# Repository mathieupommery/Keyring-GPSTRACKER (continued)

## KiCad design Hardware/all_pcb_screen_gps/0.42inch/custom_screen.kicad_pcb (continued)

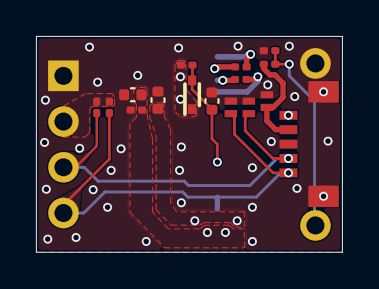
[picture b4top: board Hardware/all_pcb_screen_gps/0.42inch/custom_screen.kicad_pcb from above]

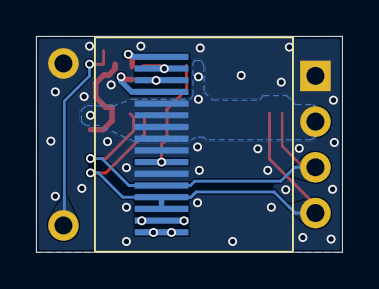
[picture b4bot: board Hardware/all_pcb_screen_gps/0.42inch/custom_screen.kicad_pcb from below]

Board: 2 copper layers, 17.0 x 12.0 mm, 18 parts (2 on the bottom side), 13 nets.

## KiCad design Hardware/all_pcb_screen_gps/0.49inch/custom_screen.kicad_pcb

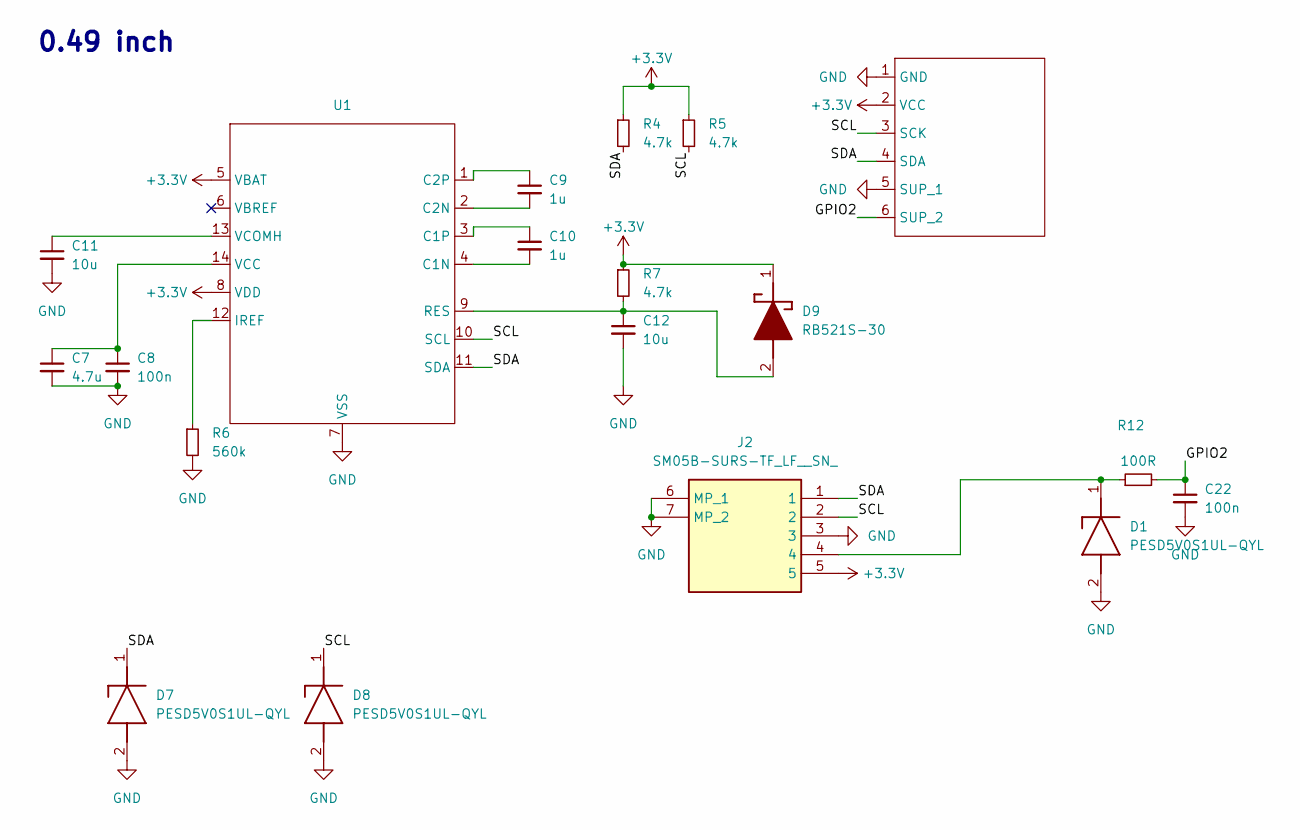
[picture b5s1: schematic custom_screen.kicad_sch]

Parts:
C7: 4.7u; C_0402_1005Metric
C8, C22: 100n; C_0201_0603Metric
C9, C10: 1u; C_0201_0603Metric
C11, C12: 10u; C_0402_1005Metric
D1, D7, D8: PESD5V0S1UL-QYL; PESD5V0S1ULQYL; Manufacturer_Part_Number PESD5V0S1UL-QYL; Mouser Part Number 771-PESD5V0S1UL-QYL
D9: RB521S-30; SODFL1608X70N; Manufacturer_Part_Number RB521S-30
J2: SM05B-SURS-TF_LF__SN_; SM05BSURSTFLFSN; Manufacturer_Part_Number SM05B-SURS-TF(LF)(SN); Mouser Part Number 306-SM05BSURSTFLFSN
R4, R5, R7: 4.7k; R_0201_0603Metric
R6: 560k; R_0201_0603Metric
R12: 100R; R_0201_0603Metric
U1: ssd1306_fpc
U4: ssd1306_5point

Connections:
+3.3V: D9.1 (K), J2.5, R4.1, R5.1, R7.1, U1.5 (VBAT), U1.8 (VDD), U4.2 (VCC)
/GPIO2: C22.1, R12.2, U4.6 (SUP_2)
/SCL: D8.1 (K), J2.2, R5.2, U1.10 (SCL), U4.3 (SCK)
/SDA: D7.1 (K), J2.1, R4.2, U1.11 (SDA), U4.4 (SDA)
GND: C7.2, C8.2, C11.2, C12.2, C22.2, D1.2 (A), D7.2 (A), D8.2 (A), J2.3, J2.6 (MP_1), J2.7 (MP_2), R6.2, U1.7 (VSS), U4.1 (GND), U4.5 (SUP_1)
unnamed: D1.1 (K), J2.4, R12.1
unnamed: C12.1, D9.2 (A), R7.2, U1.9 (RES)
unnamed: C10.2, U1.4 (C1N)
unnamed: C10.1, U1.3 (C1P)
unnamed: C9.2, U1.2 (C2N)
unnamed: C9.1, U1.1 (C2P)
unnamed: R6.1, U1.12 (IREF)
unnamed: C7.1, C8.1, U1.14 (VCC)
unnamed: C11.1, U1.13 (VCOMH)

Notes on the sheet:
0.49 inch

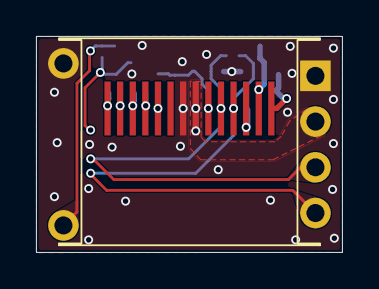
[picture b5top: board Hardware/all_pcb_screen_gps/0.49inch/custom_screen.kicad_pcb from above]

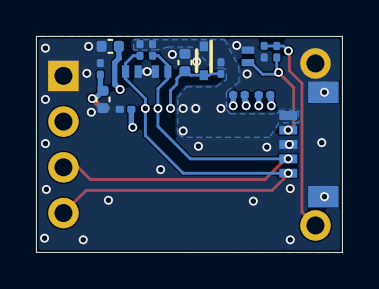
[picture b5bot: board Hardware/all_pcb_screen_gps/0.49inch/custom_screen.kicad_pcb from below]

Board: 2 copper layers, 17.0 x 12.0 mm, 19 parts (17 on the bottom side), 14 nets.

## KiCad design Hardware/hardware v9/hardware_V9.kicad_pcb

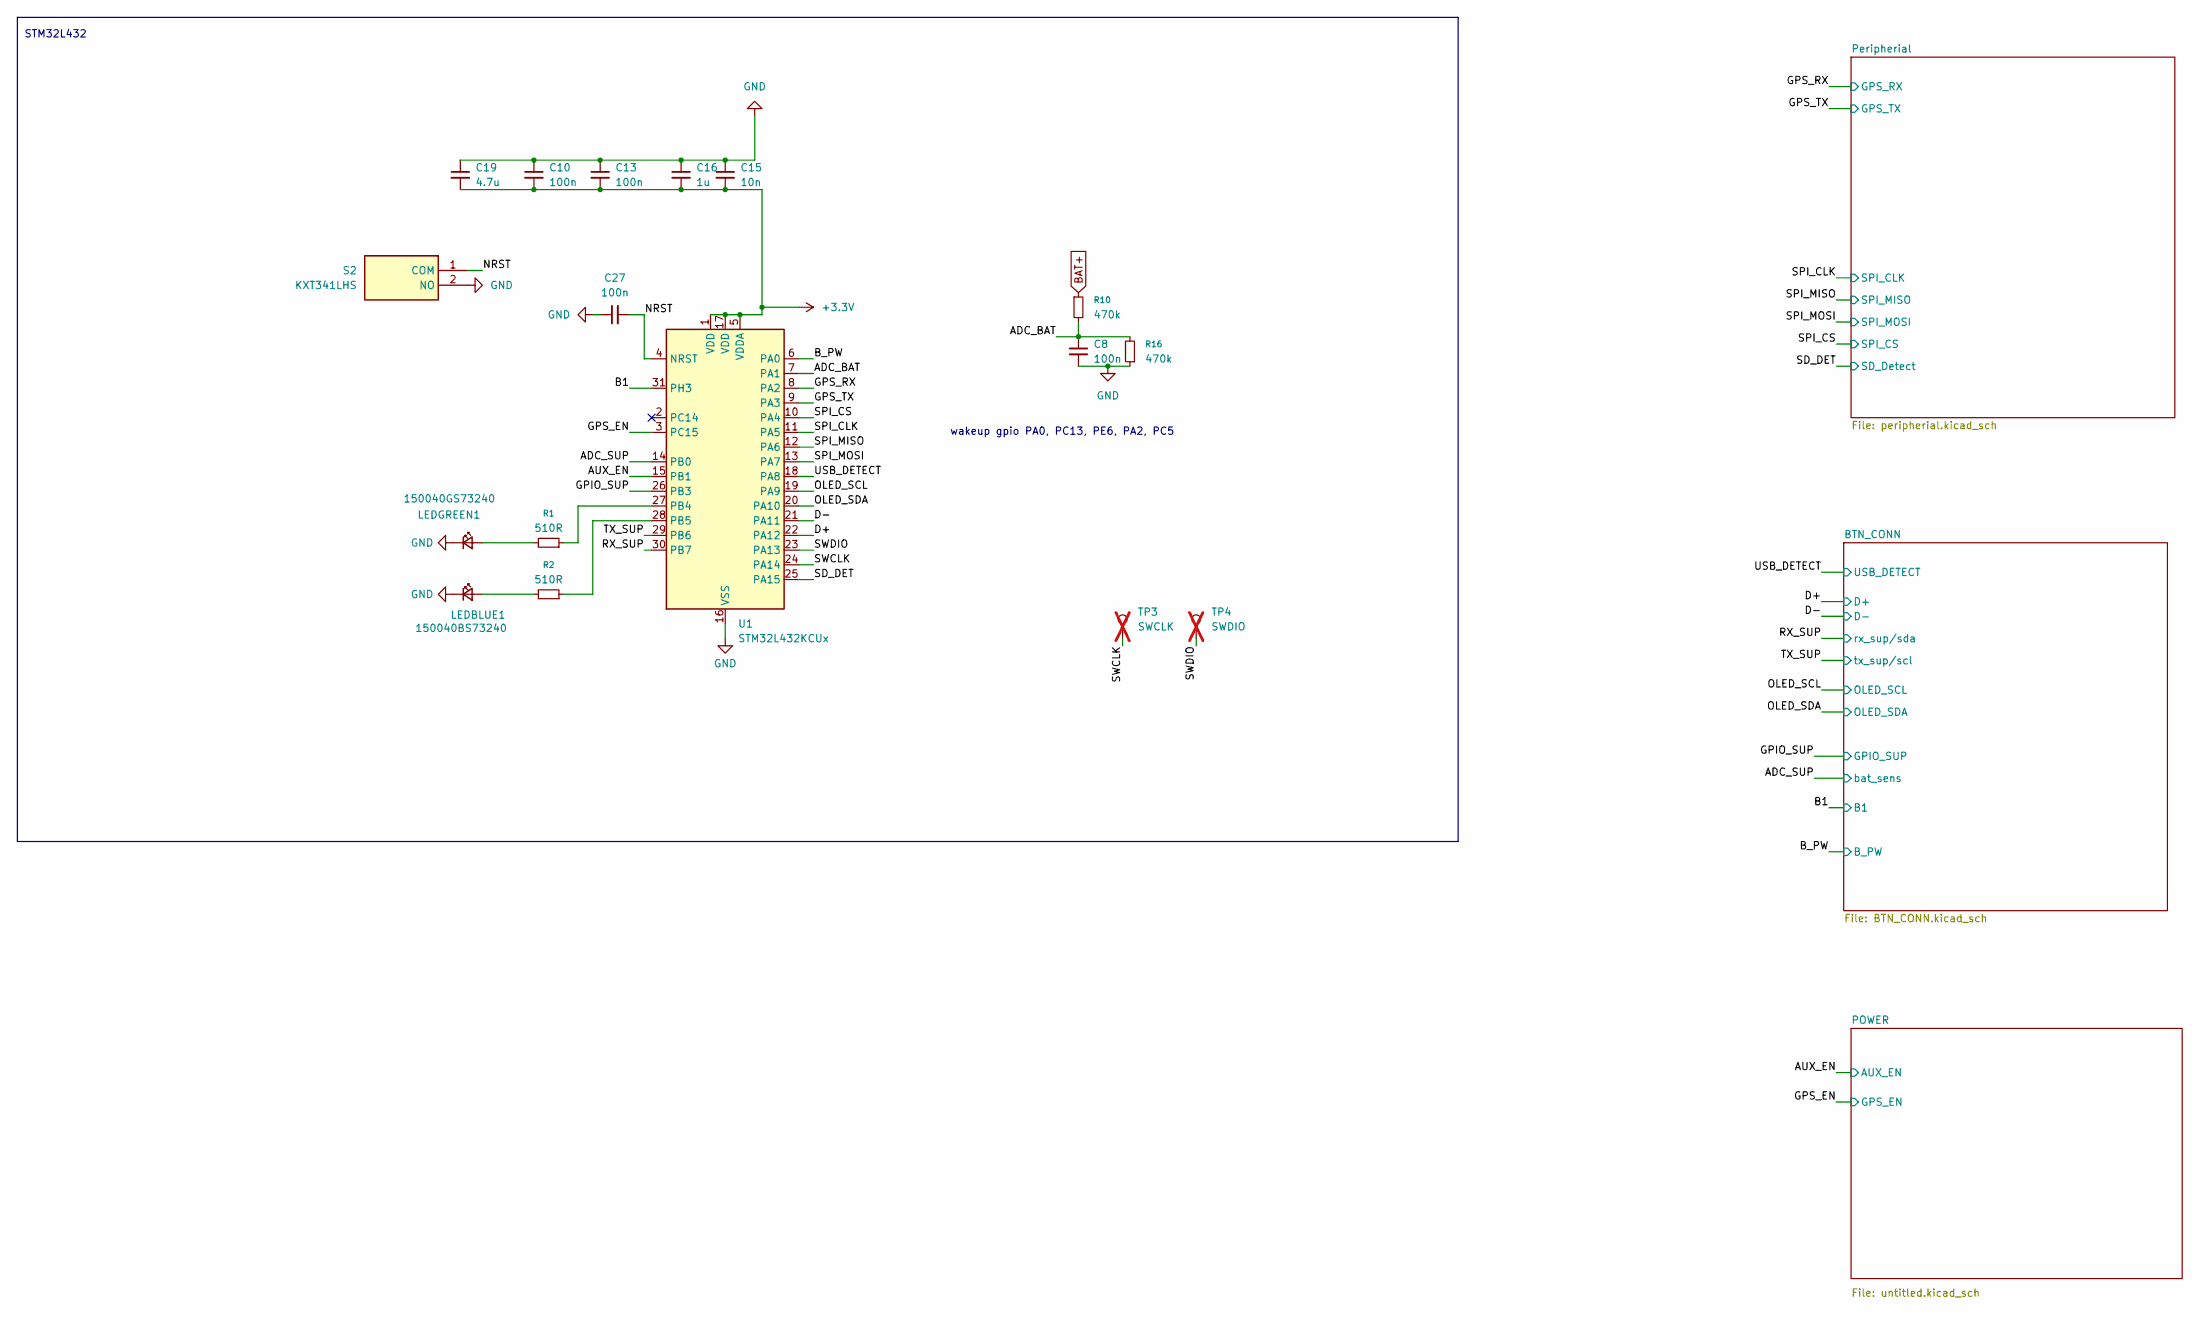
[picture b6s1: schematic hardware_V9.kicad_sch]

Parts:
C8, C10, C13, C27: 100n; C_0201_0603Metric_Pad0.64x0.40mm_HandSolder
C15: 10n; C_0201_0603Metric_Pad0.64x0.40mm_HandSolder
C16: 1u; C_0201_0603Metric_Pad0.64x0.40mm_HandSolder
C19: 4.7u; C_0402_1005Metric
LEDBLUE1: 150040BS73240; LED_0402_1005Metric; Manufacturer_Part_Number 150040BS73240; Mouser Part Number 710-150040BS73240
LEDGREEN1: 150040GS73240; LED_0402_1005Metric; Manufacturer_Part_Number 150040GS73240; Mouser Part Number 710-150040GS73240
R1, R2: 510R; R_0201_0603Metric_Pad0.64x0.40mm_HandSolder; Mouser Part Number 603-RC0201JR-07510RL
R10, R16: 470k; R_0201_0603Metric_Pad0.64x0.40mm_HandSolder; Mouser Part Number 603-AC0201FR-07470KL
S2: KXT341LHS; Manufacturer_Part_Number KXT341LHS; Mouser Part Number 611-KXT341LHS
TP3: SWCLK; pad_0.7mm; not fitted
TP4: SWDIO; pad_0.7mm; not fitted
U1: STM32L432KCUx; QFN-32-1EP_5x5mm_P0.5mm_EP3.45x3.45mm; Mouser Part Number 511-STM32L432KCU6

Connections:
+3.3V: C10.2, C13.2, C15.2, C16.2, C19.2, U1.1 (VDD), U1.5 (VDDA), U1.17 (VDD); also elsewhere on the board
/ADC_BAT: C8.1, R10.2, R16.2, U1.7 (PA1)
/ADC_SUP: U1.14 (PB0); also elsewhere on the board
/AUX_EN: U1.15 (PB1); also elsewhere on the board
/B1: U1.31 (PH3); also elsewhere on the board
/B_PW: U1.6 (PA0); also elsewhere on the board
/D+: U1.22 (PA12); also elsewhere on the board
/D-: U1.21 (PA11); also elsewhere on the board
/GPIO_SUP: U1.26 (PB3); also elsewhere on the board
/GPS_EN: U1.3 (PC15); also elsewhere on the board
/GPS_RX: U1.8 (PA2); also elsewhere on the board
/GPS_TX: U1.9 (PA3); also elsewhere on the board
/NRST: C27.2, S2.1 (COM), U1.4 (NRST)
/OLED_SCL: U1.19 (PA9); also elsewhere on the board
/OLED_SDA: U1.20 (PA10); also elsewhere on the board
/RX_SUP: U1.30 (PB7); also elsewhere on the board
/SD_DET: U1.25 (PA15); also elsewhere on the board
/SPI_CLK: U1.11 (PA5); also elsewhere on the board
/SPI_CS: U1.10 (PA4); also elsewhere on the board
/SPI_MISO: U1.12 (PA6); also elsewhere on the board
/SPI_MOSI: U1.13 (PA7); also elsewhere on the board
/SWCLK: TP3.1 (1_1), U1.24 (PA14)
/SWDIO: TP4.1 (1_1), U1.23 (PA13)
/TX_SUP: U1.29 (PB6); also elsewhere on the board
/USB_DETECT: U1.18 (PA8); also elsewhere on the board
BAT+: R10.1; also elsewhere on the board
GND: C8.2, C10.1, C13.1, C15.1, C16.1, C19.1, C27.1, LEDBLUE1.1 (K), LEDGREEN1.1 (K), R16.1, S2.2 (NO), U1.16 (VSS), U1.32 (VSS), U1.33 (VSS); also elsewhere on the board
unnamed: LEDBLUE1.2 (A), R2.2
unnamed: LEDGREEN1.2 (A), R1.2
unnamed: R1.1, U1.27 (PB4)
unnamed: R2.1, U1.28 (PB5)

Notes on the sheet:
STM32L432
wakeup gpio PA0, PC13, PE6, PA2, PC5

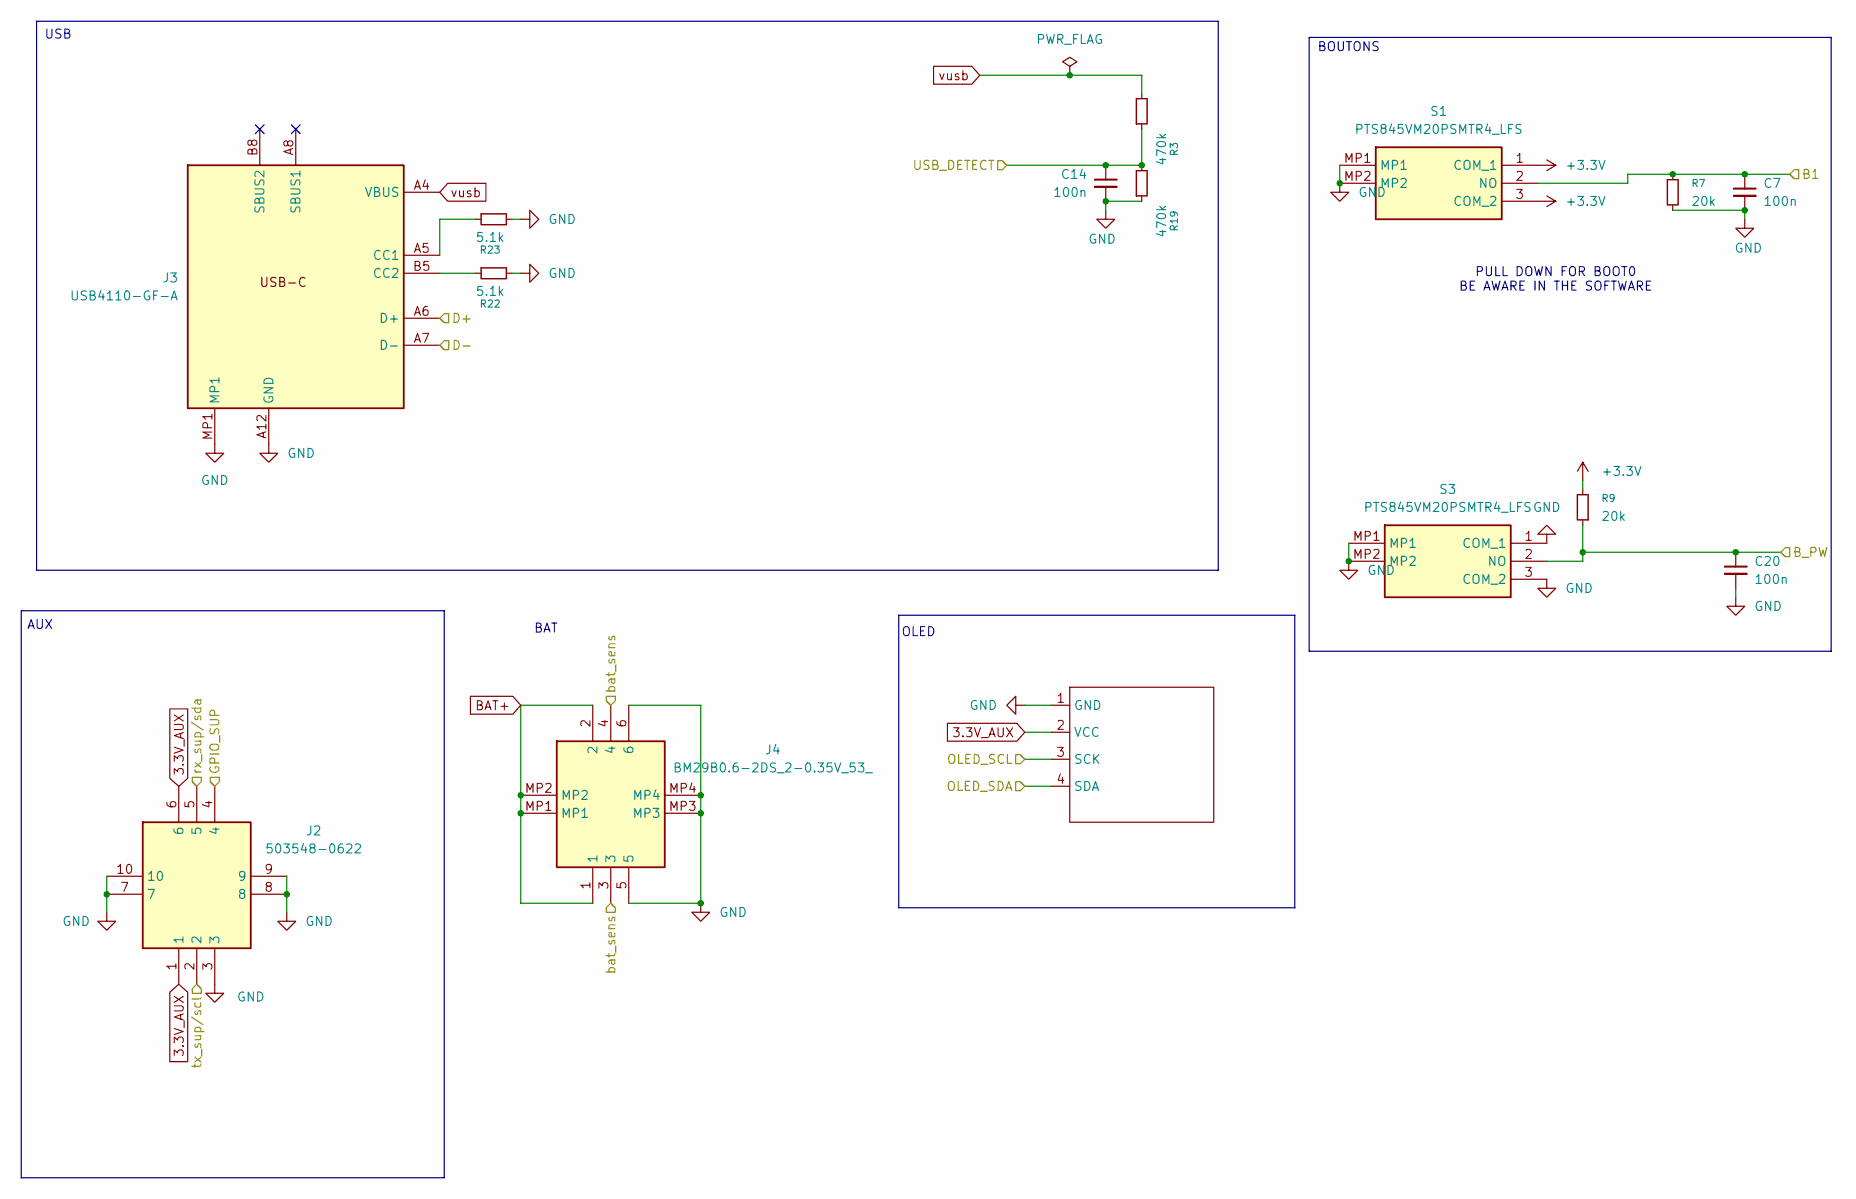
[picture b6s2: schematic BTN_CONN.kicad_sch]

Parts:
C7, C14, C20: 100n; C_0201_0603Metric_Pad0.64x0.40mm_HandSolder
J2: 503548-0622; 5035480622; Manufacturer_Part_Number 503548-0622; Mouser Part Number 538-503548-0622
J3: USB4110-GF-A; USB4110GFA; Mouser Part Number 640-USB4110-GF-A
J4: BM29B0.6-2DS_2-0.35V_53_; BM29B062DS2035V53; Manufacturer_Part_Number BM29B0.6-2DS/2-0.35V(53); Mouser Part Number 798-BM29B62DS2035V53
R3, R19: 470k; R_0201_0603Metric_Pad0.64x0.40mm_HandSolder; Mouser Part Number 603-AC0201FR-07470KL
R7, R9: 20k; R_0201_0603Metric_Pad0.64x0.40mm_HandSolder; Mouser Part Number 603-AC0201FR-0720KL
R22, R23: 5.1k; R_0201_0603Metric_Pad0.64x0.40mm_HandSolder; Mouser Part Number 603-AF0201FR-075K1L
S1, S3: PTS845VM20PSMTR4_LFS; PTS845VM20PSMTR4LFS; Manufacturer_Part_Number PTS845VM20PSMTR4 LFS; Mouser Part Number 611-PTS845VM20PSMTR4
U4: ssd1306_5point

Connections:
3.3V_AUX: J2.1, J2.6, U4.2 (VCC); also elsewhere on the board
+3.3V: R9.2, S1.1 (COM_1), S1.3 (COM_2); also elsewhere on the board
/ADC_SUP: J4.3, J4.4; also elsewhere on the board
/B1: C7.1, R7.1, S1.2 (NO); also elsewhere on the board
/B_PW: C20.1, R9.1, S3.2 (NO); also elsewhere on the board
/D+: J3.A6 (D+), J3.B6 (D+); also elsewhere on the board
/D-: J3.A7 (D-), J3.B7 (D-); also elsewhere on the board
/GPIO_SUP: J2.4; also elsewhere on the board
/OLED_SCL: U4.3 (SCK); also elsewhere on the board
/OLED_SDA: U4.4 (SDA); also elsewhere on the board
/RX_SUP: J2.5; also elsewhere on the board
/TX_SUP: J2.2; also elsewhere on the board
/USB_DETECT: C14.1, R3.1, R19.2; also elsewhere on the board
BAT+: J4.1, J4.2, J4.MP1, J4.MP2; also elsewhere on the board
GND: C7.2, C14.2, C20.2, J2.3, J2.7, J2.8, J2.9, J2.10, J3.A1 (GND), J3.A12 (GND), J3.B1 (GND), J3.B12 (GND), J3.MP1, J3.MP2, J3.MP3, J3.MP4, J4.5, J4.6, J4.MP3, J4.MP4, R7.2, R19.1, R22.2, R23.2, S1.MP1, S1.MP2, S3.1 (COM_1), S3.3 (COM_2), S3.MP1, S3.MP2, U4.1 (GND), U4.5 (GND), U4.6 (GND); also elsewhere on the board
unnamed: J3.A5 (CC1), R23.1
unnamed: J3.B5 (CC2), R22.1
vusb: J3.A4 (VBUS), J3.A9 (VBUS), J3.B4 (VBUS), J3.B9 (VBUS), R3.2; also elsewhere on the board

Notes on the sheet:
AUX
BOUTONS
USB
PULL DOWN FOR BOOT0 BE AWARE IN THE SOFTWARE
OLED
BAT

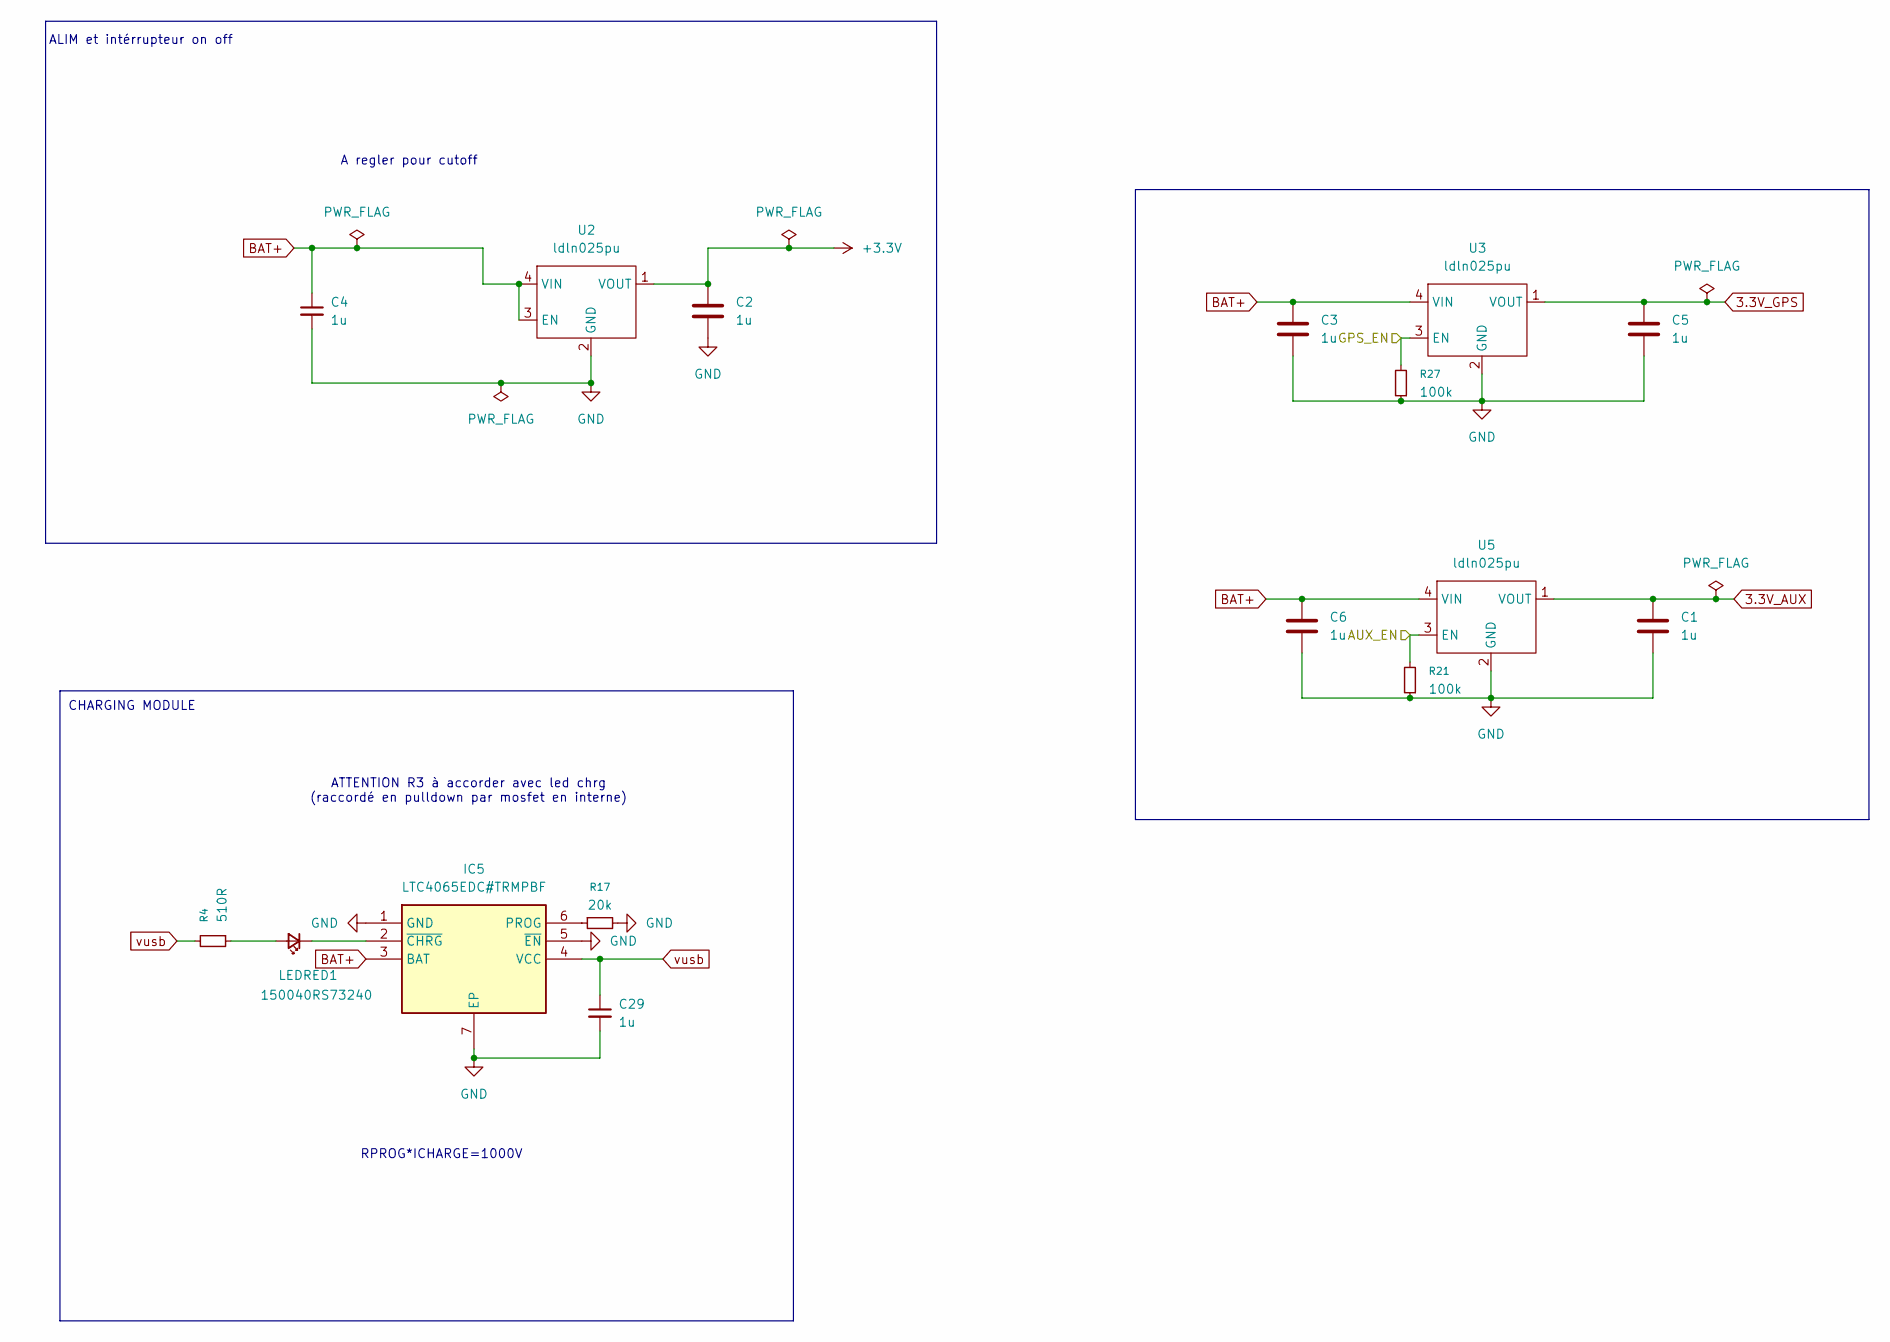
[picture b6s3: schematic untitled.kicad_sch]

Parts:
C1, C2, C3, C4, C5, C6, C29: 1u; C_0201_0603Metric_Pad0.64x0.40mm_HandSolder
IC5: LTC4065EDC#TRMPBF; SON50P200X200X80-7N-D; Manufacturer_Part_Number LTC4065EDC#TRMPBF; Mouser Part Number 584-LTC4065EDCTRMPBF
LEDRED1: 150040RS73240; LED_0402_1005Metric; Manufacturer_Part_Number 150040GS73240; Mouser Part Number 710-150040GS73240
R4: 510R; R_0201_0603Metric_Pad0.64x0.40mm_HandSolder; Mouser Part Number 603-RC0201JR-07510RL
R17: 20k; R_0201_0603Metric_Pad0.64x0.40mm_HandSolder; Mouser Part Number 603-AC0201FR-0720KL
R21, R27: 100k; R_0201_0603Metric_Pad0.64x0.40mm_HandSolder; Mouser Part Number 603-RC0201BR-07100KL
U2, U3, U5: ldln025pu; Mouser Part Number 511-LDLN025PU33R

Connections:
3.3V_AUX: C1.1, U5.1 (VOUT); also elsewhere on the board
3.3V_GPS: C5.1, U3.1 (VOUT); also elsewhere on the board
+3.3V: C2.1, U2.1 (VOUT); also elsewhere on the board
/AUX_EN: R21.2, U5.3 (EN); also elsewhere on the board
/GPS_EN: R27.2, U3.3 (EN); also elsewhere on the board
BAT+: C3.1, C4.1, C6.1, IC5.3 (BAT), U2.3 (EN), U2.4 (VIN), U3.4 (VIN), U5.4 (VIN); also elsewhere on the board
GND: C1.2, C2.2, C3.2, C4.2, C5.2, C6.2, C29.2, IC5.1 (GND), IC5.5 (~EN), IC5.7 (EP), R17.2, R21.1, R27.1, U2.2 (GND), U3.2 (GND), U5.2 (GND); also elsewhere on the board
unnamed: IC5.6 (PROG), R17.1
unnamed: IC5.2 (~CHRG), LEDRED1.1 (K)
unnamed: LEDRED1.2 (A), R4.1
vusb: C29.1, IC5.4 (VCC), R4.2; also elsewhere on the board

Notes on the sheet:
ALIM et intérrupteur on off
A regler pour cutoff
RPROG*ICHARGE=1000V
ATTENTION R3 à accorder avec led chrg (raccordé en pulldown par mosfet en interne)
CHARGING MODULE

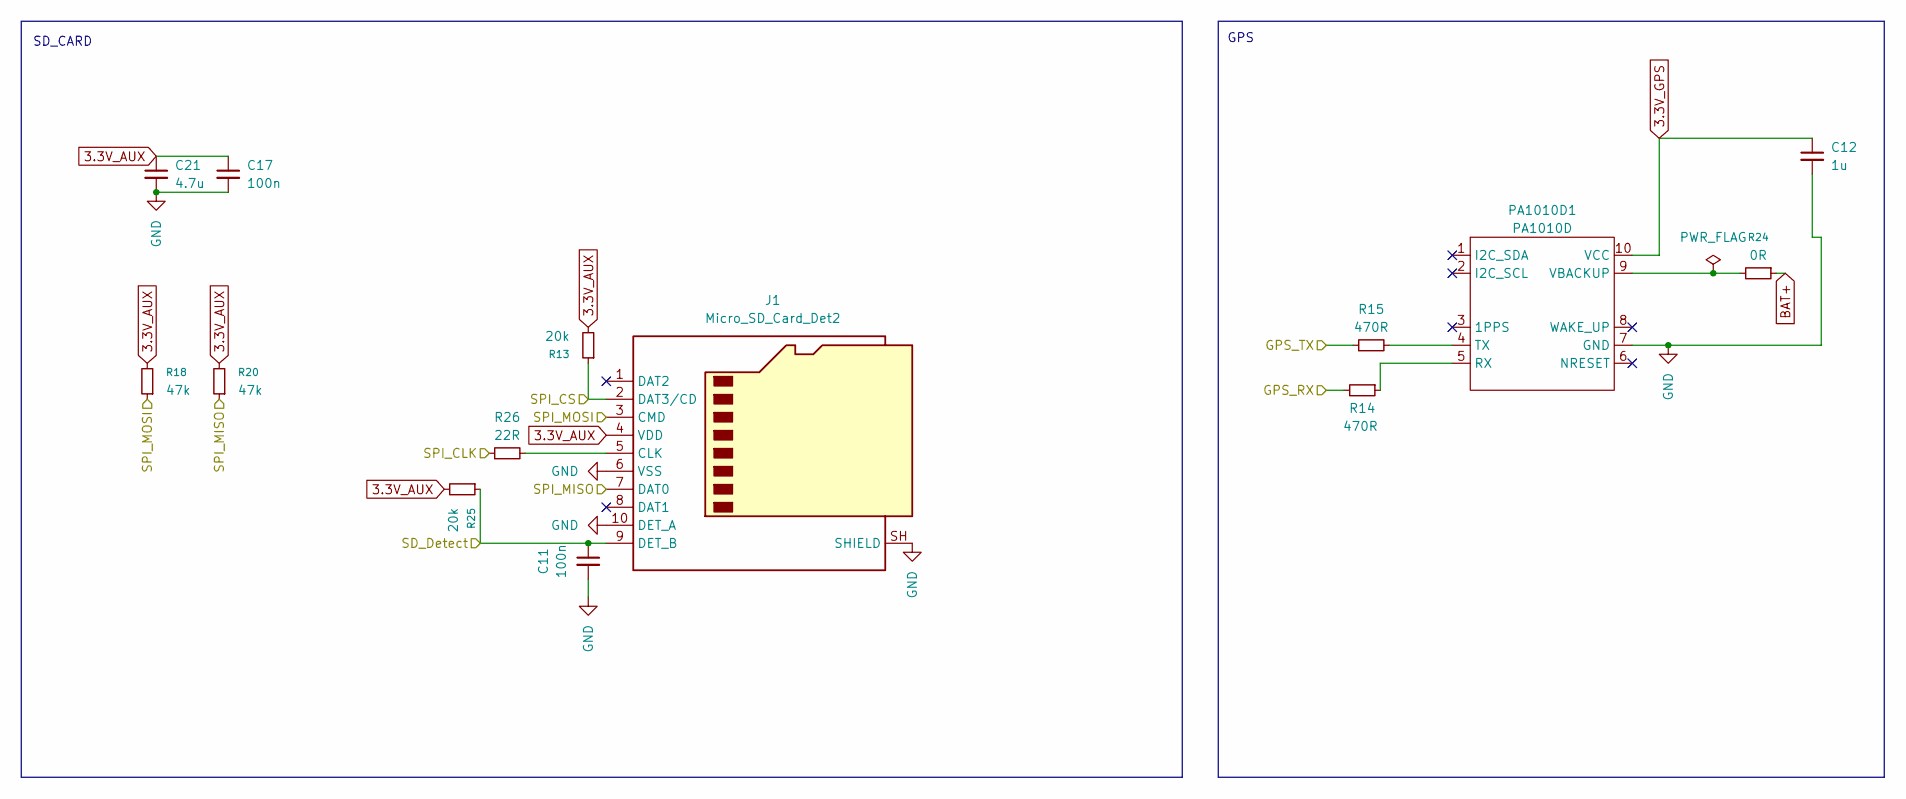
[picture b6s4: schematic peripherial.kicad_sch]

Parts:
C11, C17: 100n; C_0201_0603Metric_Pad0.64x0.40mm_HandSolder
C12: 1u; C_0201_0603Metric_Pad0.64x0.40mm_HandSolder
C21: 4.7u; LED_0402_1005Metric
J1: Micro_SD_Card_Det2; microSD_HC_Molex_104031-0811
PA1010D1: PA1010D
R13, R25: 20k; R_0201_0603Metric_Pad0.64x0.40mm_HandSolder; Mouser Part Number 603-AC0201FR-0720KL
R14, R15: 470R; R_0201_0603Metric_Pad0.64x0.40mm_HandSolder
R18, R20: 47k; R_0201_0603Metric_Pad0.64x0.40mm_HandSolder; Mouser Part Number 603-AC0201FR-0720KL
R24: 0R; R_0201_0603Metric_Pad0.64x0.40mm_HandSolder; Mouser Part Number 603-AC0201FR-07470KL
R26: 22R; R_0201_0603Metric_Pad0.64x0.40mm_HandSolder

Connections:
3.3V_AUX: C17.1, C21.1, J1.4 (VDD), R13.2, R18.2, R20.2, R25.2; also elsewhere on the board
3.3V_GPS: C12.1, PA1010D1.10 (VCC); also elsewhere on the board
/GPS_RX: R14.2; also elsewhere on the board
/GPS_TX: R15.1; also elsewhere on the board
/SD_DET: C11.1, J1.9 (DET_B), R25.1; also elsewhere on the board
/SPI_CLK: R26.1; also elsewhere on the board
/SPI_CS: J1.2 (DAT3/CD), R13.1; also elsewhere on the board
/SPI_MISO: J1.7 (DAT0), R20.1; also elsewhere on the board
/SPI_MOSI: J1.3 (CMD), R18.1; also elsewhere on the board
BAT+: R24.1; also elsewhere on the board
GND: C11.2, C12.2, C17.2, C21.2, J1.6 (VSS), J1.10 (DET_A), J1.SH (SHIELD), PA1010D1.7 (GND); also elsewhere on the board
unnamed: J1.5 (CLK), R26.2
unnamed: PA1010D1.5 (RX), R14.1
unnamed: PA1010D1.4 (TX), R15.2
unnamed: PA1010D1.9 (VBACKUP), R24.2

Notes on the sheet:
SD_CARD
GPS

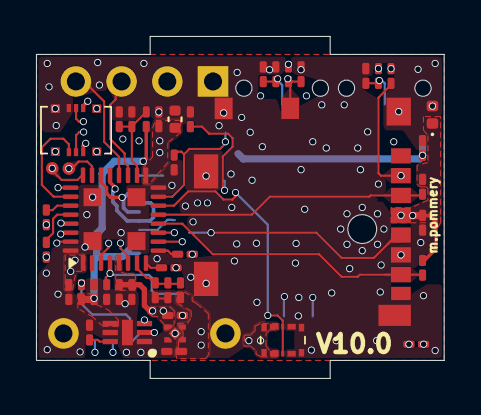
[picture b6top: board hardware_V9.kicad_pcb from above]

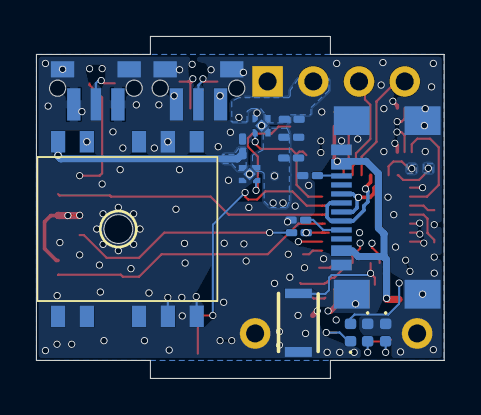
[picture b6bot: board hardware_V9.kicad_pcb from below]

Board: 6 copper layers, 22.7 x 19.0 mm, 62 parts (18 on the bottom side), 43 nets.

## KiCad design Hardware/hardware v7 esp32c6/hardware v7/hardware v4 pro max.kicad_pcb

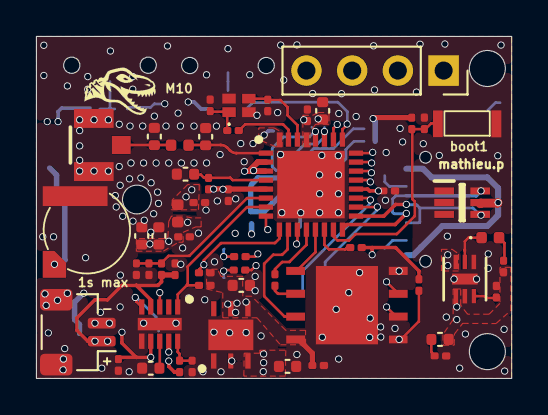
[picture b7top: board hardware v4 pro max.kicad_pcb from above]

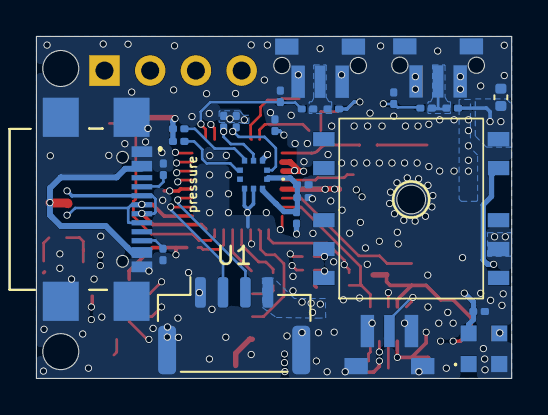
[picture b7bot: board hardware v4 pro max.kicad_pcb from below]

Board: 6 copper layers, 26.4 x 19.0 mm, 80 parts (26 on the bottom side), 52 nets.

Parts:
BT1: ML414S; MS421R-IV03E
C2, C8: 15p; C_0201_0603Metric
C3, C4, C5, C10, C12, C16, C20, C23: 1u; C_0402_1005Metric
C6, C7, C15, C18, C24, C30: 10n; C_0201_0603Metric
C11, C13, C14, C19, C21, C22, C25, C26, C29: 100n; C_0201_0603Metric
C17: 10u; C_0402_1005Metric
C27, C28: TBD; C_0402_1005Metric
D1: LED_0402_1005Metric
D6: 82400274; SOT65P210X110-6N
IC1: ESP32-C6FH4; QFN50P500X500X90-33N
IC2: W25Q128JVPIQ_TR; SON127P600X500X80-9N-D
IC3: LDO40LPU33RY; SON95P300X300X90-7N-D
IC4: LTC2955CDDB-1#TRMPBF; SON50P200X300X80-11N-D
J2: 636101111001
J3: OLED; PinSocket_1x04_P2.54mm_Vertical
J4: USB_C_Receptacle_USB2.0_14P; USB4110GFA
L1: 2nH; L_0402_1005Metric
L2: TBD; L_0402_1005Metric
LED1: 587-1024-147F; 5871024147F
PA1010D1: PA1010D
R3, R29, R30, R31, R32: 20k; R_0201_0603Metric
R4: 1R; R_0201_0603Metric
R5: 510R; R_0201_0603Metric
R6: 470k; R_0201_0603Metric
R7, R8, R9, R10, R13, R16, R22, R24, R28: 10k; R_0201_0603Metric
R11, R12: 470R; R_0201_0603Metric
R14, R15: 5.1k; R_0201_0603Metric
R17, R18: 50k; R_0201_0603Metric
R19: 10R; R_0201_0603Metric
R20, R23: 2.2k; R_0201_0603Metric
R21, R25, R26: 20R; R_0201_0603Metric
S1, S2, S3: PTS845VM20PSMTR4_LFS; PTS845VM20PSMTR4LFS
SW4: boot; SW_KXT3
U1: JST_GH_SM04B-GHS-TB_1x04-1MP_P1.25mm_Horizontal
U2: LTC4065AEDC; DFN-6_DC_LIT
U3: JST_SH_BM02B-SRSS-TB_1x02-1MP_P1.00mm_Vertical
U5: BMP581
Y1: LFXTAL069527REEL

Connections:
+3.3V: C5.1, C10.1, C11.1, C12.1, C15.1, C16.1, C17.1, C21.1, C22.1, C25.1, C29.1, C30.1, IC1.5 (VDDPST1), IC1.20 (VDDPST2), IC1.29 (VDDA1), IC1.32 (VDDA2), IC2.8 (VCC), IC3.4 (VOUT), IC3.5 (VSENSE), J3.2, L1.1, LED1.2 (VDD), PA1010D1.10 (VCC), R7.1, R8.1, R13.2, R16.1, R19.1, R20.1, R22.2, R23.2, R24.1, R25.1, R28.1, R31.2, R32.2, U1.4
B1: C7.1, IC1.26 (SDIO_DATA1), R10.2
B2: C6.1, IC1.25 (SDIO_DATA0), R9.2
BAT+: C4.1, C24.2, IC3.3 (VIN), IC4.4 (VIN), R17.1, U2.3 (BAT), U3.1
BOOT0: IC1.14 (GPIO8), R28.2
BOOT1: C18.2, IC1.15 (GPIO9), R16.2, SW4.2
CHIP_PU: C20.1, IC1.4 (CHIP_PU), R25.2
D+: D6.4 (I/O_3), IC1.17 (GPIO13), J4.A6 (D+), J4.B6 (D+)
D-: D6.6 (I/O_4), IC1.16 (GPIO12), J4.A7 (D-), J4.B7 (D-)
EN: IC3.2 (EN), IC4.3 (EN)
FSPICLK: IC2.6 (CLK), R26.1
FSPICS2: IC1.23 (SDIO_CMD), IC2.1 (~CS), R13.1
FSPID: IC1.13 (MTDO), IC2.5 (DI_(IO0))
FSPIHD: IC1.10 (MTMS), IC2.7 (~HOLD_OR_RESET_(IO3))
FSPIQ: IC1.8 (GPIO2), IC2.2 (DO_(IO1))
FSPIWP: IC1.11 (MTDI), IC2.3 (~WP_(IO2))
GND: BT1.2 (-), C2.1, C4.2, C5.2, C6.2, C7.2, C8.2, C10.2, C11.2, C12.2, C13.2, C14.2, C15.2, C16.2, C17.2, C18.1, C19.2, C20.2, C21.2, C22.2, C23.2, C24.1, C25.2, C26.2, C27.2, C28.2, C29.2, C30.2, D6.2 (GND), IC1.33 (GND), IC2.4 (GND), IC2.9 (EP), IC3.1 (GND), IC3.7 (EP), IC4.6 (GND_1), IC4.11 (GND_2), J2.1, J2.2, J3.1, J4.A1 (GND), J4.A12 (GND), J4.B1 (GND), J4.B12 (GND), J4.MP1, J4.MP2, J4.MP3, J4.MP4, LED1.4 (GND), PA1010D1.7 (GND), R3.1, R4.2, R6.1, R14.2, R15.2, R18.2, R29.1, S1.1 (COM_1), S1.3 (COM_2), S1.MP1, S1.MP2, S2.1 (COM_1), S2.3 (COM_2), S2.MP1, S2.MP2, S3.1 (COM_1), S3.3 (COM_2), S3.MP1, S3.MP2, SW4.1, U1.1, U1.MP, U2.1 (GND), U2.5 (*EN/*ACPR), U2.7 (S), U3.2, U3.MP, U5.3 (VSS_1), U5.8 (VSS_2), U5.9 (VSS_3), Y1.2 (GND_1), Y1.4 (GND_2)
GPIO_SUP_1: IC1.18 (GPIO14), U1.2
GPIO_SUP_2: IC1.19 (GPIO15), U1.3
GPSRX: IC1.21 (U0TXD), R11.2
GPSTX: IC1.22 (U0RXD), R12.1
HSE_IN: C8.1, IC1.30 (XTAL_N), Y1.3 (CRYSTAL__2)
HSE_OUT: IC1.31 (XTAL_P), R21.1
INT: IC1.7 (XTAL_32K_N), IC4.1 (~INT), R32.1
KILL: IC1.9 (GPIO3), IC4.9 (~KILL), R31.1
LED_PWM: IC1.24 (SDIO_CLK), LED1.3 (DIN)
unnamed: BT1.1 (+), PA1010D1.9 (VBACKUP)
unnamed: C3.2, R4.1
unnamed: C27.1, J2.3, L2.1
unnamed: D1.2 (A), R5.2
unnamed: D1.1 (K), U2.2 (*CHRG)
unnamed: C28.1, IC1.1 (ANT), L2.2
unnamed: IC1.12 (MTCK), R26.2
unnamed: C26.1, IC1.2 (VDDA3P3_1), IC1.3 (VDDA3P3_2), L1.2
unnamed: IC4.10 (ON), R29.2, R30.1
unnamed: C23.1, IC4.8 (TMR)
unnamed: IC4.5 (~PB), S3.2 (NO)
unnamed: J4.A5 (CC1), R14.1
unnamed: J4.B5 (CC2), R15.1
unnamed: PA1010D1.5 (RX), R11.1
unnamed: PA1010D1.4 (TX), R12.2
unnamed: R7.2, R10.1, S1.2 (NO)
unnamed: R8.2, R9.1, S2.2 (NO)
unnamed: R3.2, U2.6 (PROG)
unnamed: R24.2, U5.6 (CSB)
unnamed: R22.1, U5.5 (SDO)
unnamed: C14.1, C19.1, R19.2, U5.1 (VDDIO), U5.10 (VDD)
unnamed: C2.2, R21.2, Y1.1 (CRYSTAL__1)
OLED_SCL: IC1.28 (SDIO_DATA3), J3.3, R20.2, U5.2 (SCK)
OLED_SDA: IC1.27 (SDIO_DATA2), J3.4, R23.1, U5.4 (SDI)
VBAT_ADC: C13.1, IC1.6 (XTAL_32K_P), R17.2, R18.1
vusb: C3.1, D6.5 (VDD), IC4.7 (SEL), J4.A4 (VBUS), J4.A9 (VBUS), J4.B4 (VBUS), J4.B9 (VBUS), R5.1, R6.2, R30.2, U2.4 (VCC)

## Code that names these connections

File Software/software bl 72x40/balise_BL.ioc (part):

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Mcu.Name=STM32WB55CGUx
Mcu.Package=UFQFPN48
Mcu.UserName=STM32WB55CGUx
PA0.Signal=GPIO_Output
PA1.Mode=Full_Duplex_Master
PA1.Signal=SPI1_SCK
PA10.Mode=Asynchronous
PA10.Signal=USART1_RX
PA11.Mode=Device
PA11.Signal=USB_DM
PA12.Mode=Device
PA12.Signal=USB_DP
PA13.Mode=Trace_Asynchronous_SW
PA13.Signal=SYS_JTMS-SWDIO
PA14.Mode=Trace_Asynchronous_SW
PA14.Signal=SYS_JTCK-SWCLK
PA2.Mode=Asynchronous
PA2.Signal=LPUART1_TX
PA3.Mode=Asynchronous
PA3.Signal=LPUART1_RX
PA4.Signal=ADCx_IN9
PA5.Signal=GPXTI5
PA6.Mode=Full_Duplex_Master
PA6.Signal=SPI1_MISO
PA7.Mode=I2C
PA7.Signal=I2C3_SCL
PA9.Mode=Asynchronous
PA9.Signal=USART1_TX
PB0.GPIOParameters=GPIO_Label
PB0.GPIO_Label=LED0
PB0.Signal=GPIO_Output
PB1.GPIOParameters=GPIO_Label
PB1.GPIO_Label=LED1
PB1.Signal=GPIO_Output
PB3.Mode=Trace_Asynchronous_SW
PB3.Signal=SYS_JTDO-SWO
PB4.Mode=I2C
PB4.Signal=I2C3_SDA
PB5.Mode=Full_Duplex_Master
PB5.Signal=SPI1_MOSI
PB6.Signal=GPXTI6
PB7.GPIOParameters=GPIO_Label
PB7.GPIO_Label=SPI_CS
PB7.Signal=GPIO_Output
PB8.Mode=I2C
PB8.Signal=I2C1_SCL
PB9.Mode=I2C
PB9.Signal=I2C1_SDA
PC14-OSC32_IN.GPIOParameters=GPIO_ModeDefaultEXTI
PC14-OSC32_IN.GPIO_ModeDefaultEXTI=GPIO_MODE_IT_RISING_FALLING
PC14-OSC32_IN.Signal=GPXTI14
PC15-OSC32_OUT.GPIOParameters=GPIO_ModeDefaultEXTI
PC15-OSC32_OUT.GPIO_ModeDefaultEXTI=GPIO_MODE_IT_RISING_FALLING
PC15-OSC32_OUT.Signal=GPXTI15
RCC.HSE_VALUE=32000000
RCC.SYSCLKFreq_VALUE=64000000
RCC.SYSCLKSource=RCC_SYSCLKSOURCE_PLLCLK
board=custom

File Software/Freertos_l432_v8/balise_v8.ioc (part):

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Mcu.Name=STM32L432K(B-C)Ux
Mcu.Package=UFQFPN32
Mcu.UserName=STM32L432KCUx
PA0.GPIOParameters=GPIO_Label,GPIO_ModeDefaultEXTI
PA0.GPIO_Label=PWR_BTN
PA0.GPIO_ModeDefaultEXTI=GPIO_MODE_IT_RISING_FALLING
PA0.Signal=GPXTI0
PA1.Signal=ADCx_IN6
PA10.Mode=I2C
PA10.Signal=I2C1_SDA
PA11.Mode=Device
PA11.Signal=USB_DM
PA12.Mode=Device
PA12.Signal=USB_DP
PA13\ (JTMS-SWDIO).Mode=Serial_Wire
PA13\ (JTMS-SWDIO).Signal=SYS_JTMS-SWDIO
PA14\ (JTCK-SWCLK).Mode=Serial_Wire
PA14\ (JTCK-SWCLK).Signal=SYS_JTCK-SWCLK
PA15\ (JTDI).GPIOParameters=GPIO_Label
PA15\ (JTDI).GPIO_Label=SD_DET
PA15\ (JTDI).Signal=GPIO_Input
PA2.Mode=Asynchronous
PA2.Signal=LPUART1_TX
PA3.Mode=Asynchronous
PA3.Signal=LPUART1_RX
PA4.GPIOParameters=GPIO_Label
PA4.GPIO_Label=FLASH_CS
PA4.Signal=GPIO_Output
PA5.Mode=Full_Duplex_Master
PA5.Signal=SPI1_SCK
PA6.Mode=Full_Duplex_Master
PA6.Signal=SPI1_MISO
PA7.Mode=Full_Duplex_Master
PA7.Signal=SPI1_MOSI
PA8.GPIOParameters=GPIO_Label
PA8.GPIO_Label=USB_DET
PA8.Signal=GPIO_Input
PA9.Mode=I2C
PA9.Signal=I2C1_SCL
PB1.GPIOParameters=GPIO_Label
PB1.GPIO_Label=AUX_EN
PB1.Signal=GPIO_Output
PB4\ (NJTRST).GPIOParameters=GPIO_Label
PB4\ (NJTRST).GPIO_Label=LED_GREEN
PB4\ (NJTRST).Signal=GPIO_Output
PB5.GPIOParameters=GPIO_Label
PB5.GPIO_Label=LED_BLUE
PB5.Signal=GPIO_Output
PC15-OSC32_OUT\ (PC15).GPIOParameters=GPIO_Label
PC15-OSC32_OUT\ (PC15).GPIO_Label=GPS_EN
PC15-OSC32_OUT\ (PC15).Signal=GPIO_Output
PH3-BOOT0.GPIOParameters=GPIO_PuPd,GPIO_Label,GPIO_ModeDefaultEXTI
PH3-BOOT0.GPIO_Label=B2
PH3-BOOT0.GPIO_ModeDefaultEXTI=GPIO_MODE_IT_RISING_FALLING
PH3-BOOT0.GPIO_PuPd=GPIO_NOPULL
PH3-BOOT0.Signal=GPXTI3
RCC.HSE_VALUE=8000000
RCC.SYSCLKFreq_VALUE=80000000
RCC.SYSCLKSource=RCC_SYSCLKSOURCE_PLLCLK
board=custom

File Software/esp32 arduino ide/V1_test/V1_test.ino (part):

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#define SCREEN_HEIGHT 64
#define OLED_RESET -1

#define GPS_RX_PIN 17
#define GPS_TX_PIN 16
#define GPS_BAUD   115200
#define BUTTON_PIN 21

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
#define FLASH_CS 18

#define GPIO_SUP_2 15
#define GPIO_SUP_1 14

#define FLASH_MOSI 7
#define FLASH_MISO 2
#define FLASH_HOLD 4
#define FLASH_WP 5

#define KILL_PIN 3
#define ADC_PIN 0
#define INT_POWER_PIN 1

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	display.UpdateScreen();

  Serial.begin(115200);
  GPS_Serial.begin(GPS_BAUD, SERIAL_8N1, GPS_RX_PIN, GPS_TX_PIN);

  pinMode(BTN_A_PIN, INPUT_PULLUP);
  pinMode(BTN_B_PIN, INPUT_PULLUP);
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
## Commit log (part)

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2024-08-03 fhui
    fsui
2024-08-20 updfate
2024-08-27 add temperature sensor
2024-09-24 usb com device
2024-10-06 hardware v3
2024-10-11 commit before flash
2024-10-30 mode balise
    implementation du mode balise dans la memoire flash
2024-11-01 balise gps improvment
2024-11-02 step
2024-11-02 step file
2024-11-02 3d pcb v3
2024-11-03 python
2024-11-03 add enline usb
2024-11-03 distanceparcouru
2024-11-04 dist
2024-11-05 bug fix
2024-11-08 pcb v4 with ble
2024-11-10 bug corrections
2024-11-10 code
2024-11-17 hfgd
2024-11-21 textscroll add
2024-11-23 add usb monitorin,g
2024-11-23 pythonfile
2024-11-28 ajout tarvos pour test
2024-12-10 v0.0.1 software bluetooth
2024-12-17 board v5 gps 25Hz !!
2024-12-29 screen update
2025-02-23 yhry
2025-06-07 update code now on freertos with 10hz gps and 5hz balise
2025-06-12 hardware v7 esp32
